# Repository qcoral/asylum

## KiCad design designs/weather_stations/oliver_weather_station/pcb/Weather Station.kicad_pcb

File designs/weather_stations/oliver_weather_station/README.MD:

# Oliver's Weather Station
A very basic prototype of a weather station using a Wemos C3 Mini and a 1.8" TFT display. 
Code will be heavily improved once I have access to the physical hardware to test!

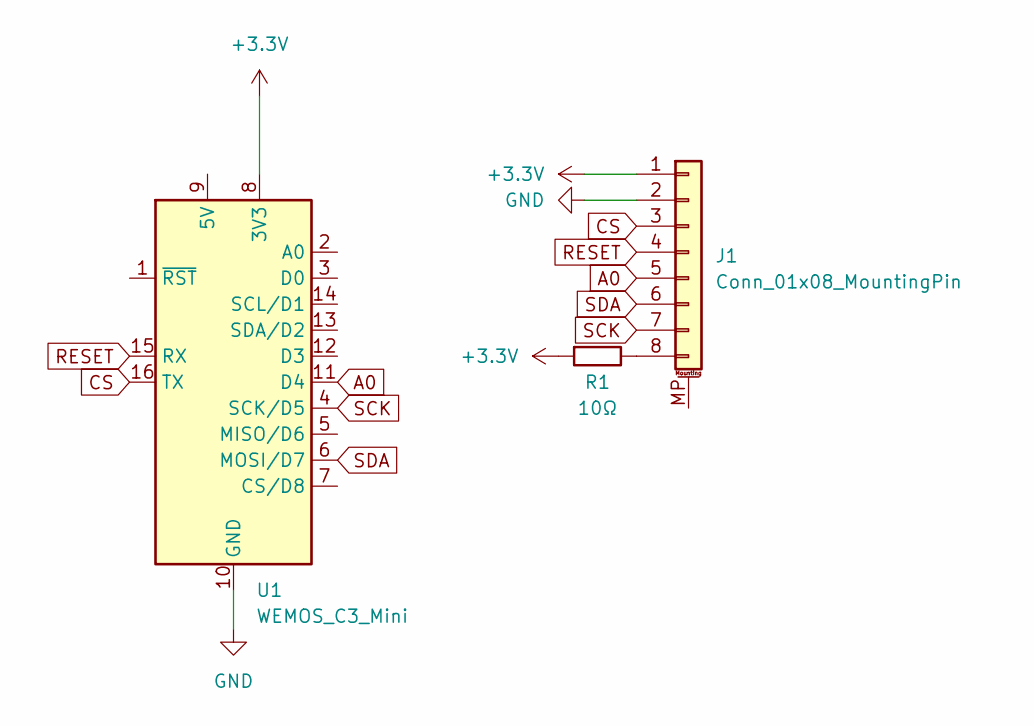
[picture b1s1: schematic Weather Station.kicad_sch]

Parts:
J1: Conn_01x08_MountingPin; PinHeader_1x08_P2.54mm_Vertical
R1: 10Ω; R_Axial_DIN0207_L6.3mm_D2.5mm_P10.16mm_Horizontal
U1: WEMOS_C3_Mini; WEMOS_D1_mini_light

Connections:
+3.3V: J1.1, R1.1, U1.8 (3V3)
A0: J1.5, U1.11 (D4)
CS: J1.3, U1.16 (TX)
GND: J1.2, U1.10 (GND)
unnamed: J1.8, R1.2
RESET: J1.4, U1.15 (RX)
SCK: J1.7, U1.4 (SCK/D5)
SDA: J1.6, U1.6 (MOSI/D7)

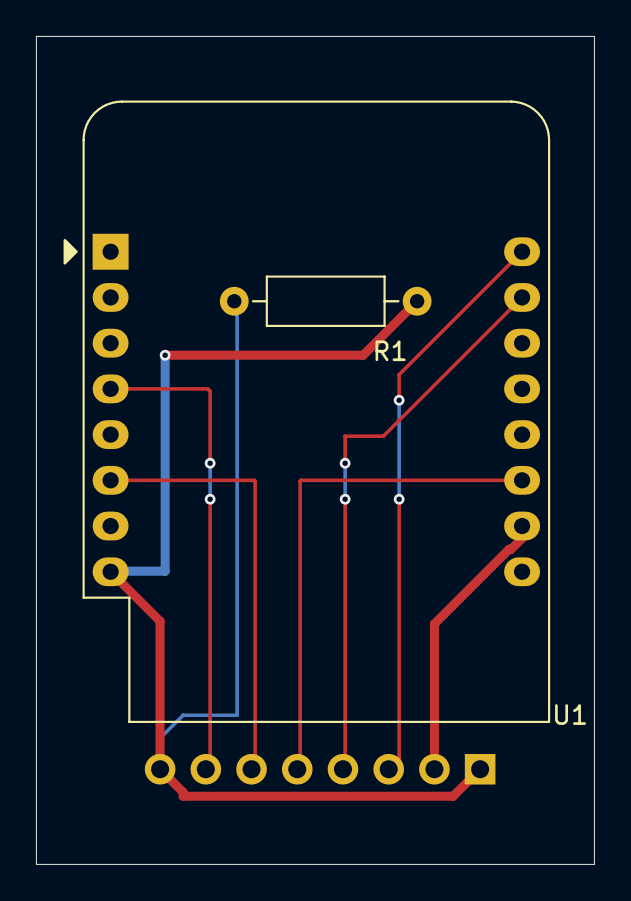
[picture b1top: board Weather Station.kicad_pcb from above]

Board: 2 copper layers, 31.0 x 46.0 mm, 3 parts (1 on the bottom side), 8 nets.

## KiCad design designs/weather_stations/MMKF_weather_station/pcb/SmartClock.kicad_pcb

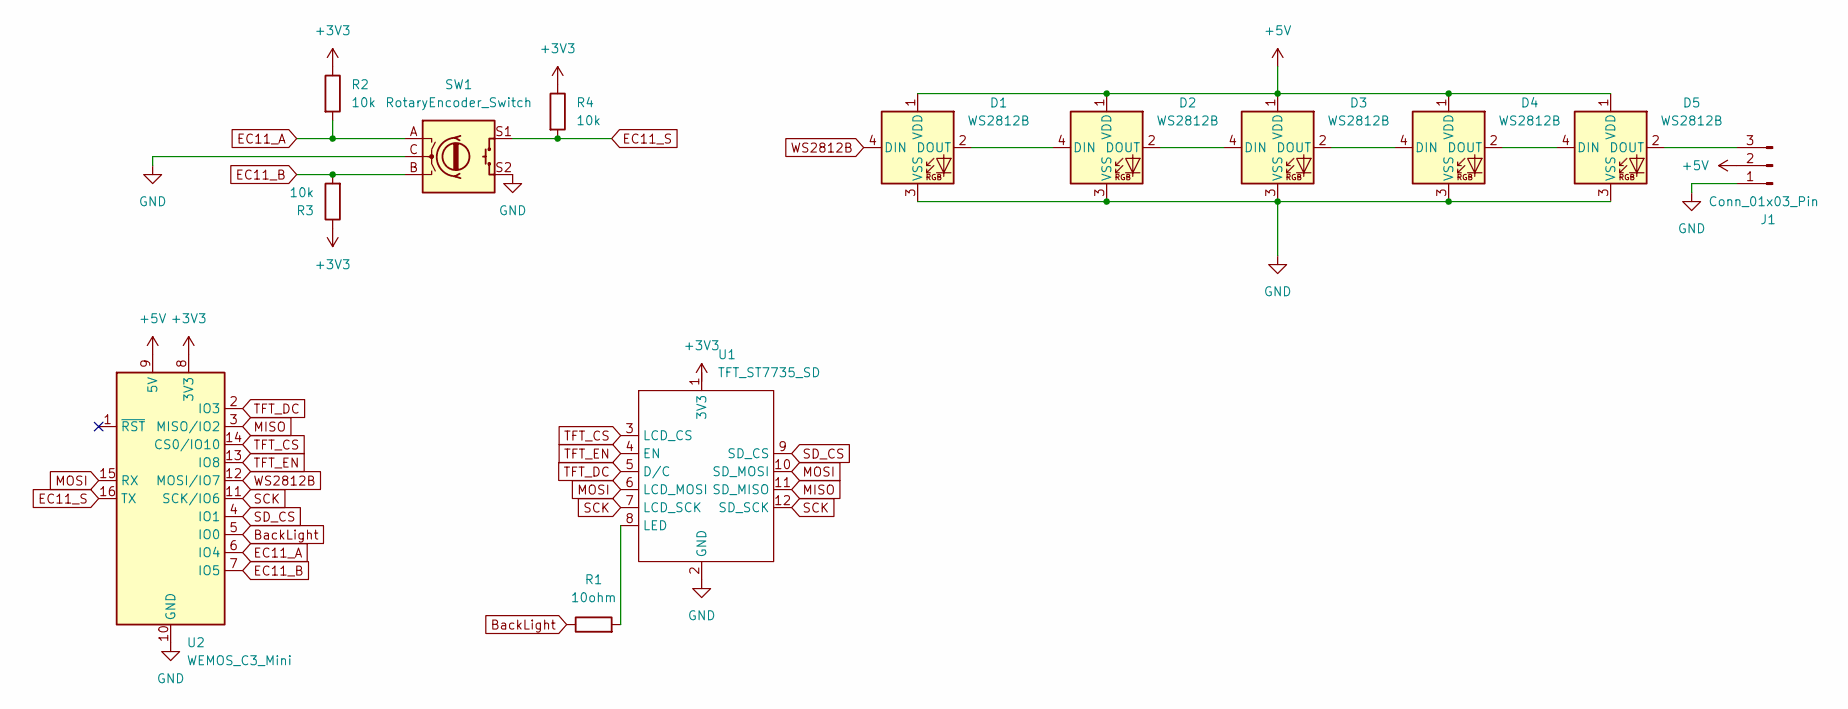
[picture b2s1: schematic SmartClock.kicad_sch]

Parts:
D1, D2, D3, D4, D5: WS2812B; LED_WS2812B_PLCC4_5.0x5.0mm_P3.2mm
J1: Conn_01x03_Pin; PinHeader_1x03_P2.54mm_Vertical
R1: 10ohm; Resistor_0402
R2, R3, R4: 10k; Resistor_0402
SW1: RotaryEncoder_Switch; RotaryEncoder_Alps_EC11E-Switch_Vertical_H20mm
U1: TFT_ST7735_SD
U2: WEMOS_C3_Mini; WEMOS_D1_mini_light

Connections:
+3V3: R2.1, R3.1, R4.1, U2.8 (3V3)
+5V: D1.1 (VDD), D2.1 (VDD), D3.1 (VDD), D4.1 (VDD), D5.1 (VDD), J1.2, U2.9 (5V)
BackLight: R1.1, U2.5 (IO0)
EC11_A: R2.2, SW1.A, U2.6 (IO4)
EC11_B: R3.2, SW1.B, U2.7 (IO5)
EC11_S: R4.2, SW1.S1, U2.16 (TX)
GND: D1.3 (VSS), D2.3 (VSS), D3.3 (VSS), D4.3 (VSS), D5.3 (VSS), J1.1, SW1.C, SW1.S2, U1.2 (GND), U2.10 (GND)
MISO: U1.11 (SD_MISO), U2.3 (MISO/IO2)
MOSI: U1.6 (LCD_MOSI), U1.10 (SD_MOSI), U2.15 (RX)
unnamed: D1.2 (DOUT), D2.4 (DIN)
unnamed: D2.2 (DOUT), D3.4 (DIN)
unnamed: D3.2 (DOUT), D4.4 (DIN)
unnamed: D4.2 (DOUT), D5.4 (DIN)
unnamed: D5.2 (DOUT), J1.3
unnamed: R1.2, U1.8 (LED)
SCK: U1.7 (LCD_SCK), U1.12 (SD_SCK), U2.11 (SCK/IO6)
SD_CS: U1.9 (SD_CS), U2.4 (IO1)
TFT_CS: U1.3 (LCD_CS), U2.14 (CS0/IO10)
TFT_DC: U1.5 (D/C), U2.2 (IO3)
TFT_EN: U1.4 (EN), U2.13 (IO8)
WS2812B: D1.4 (DIN), U2.12 (MOSI/IO7)

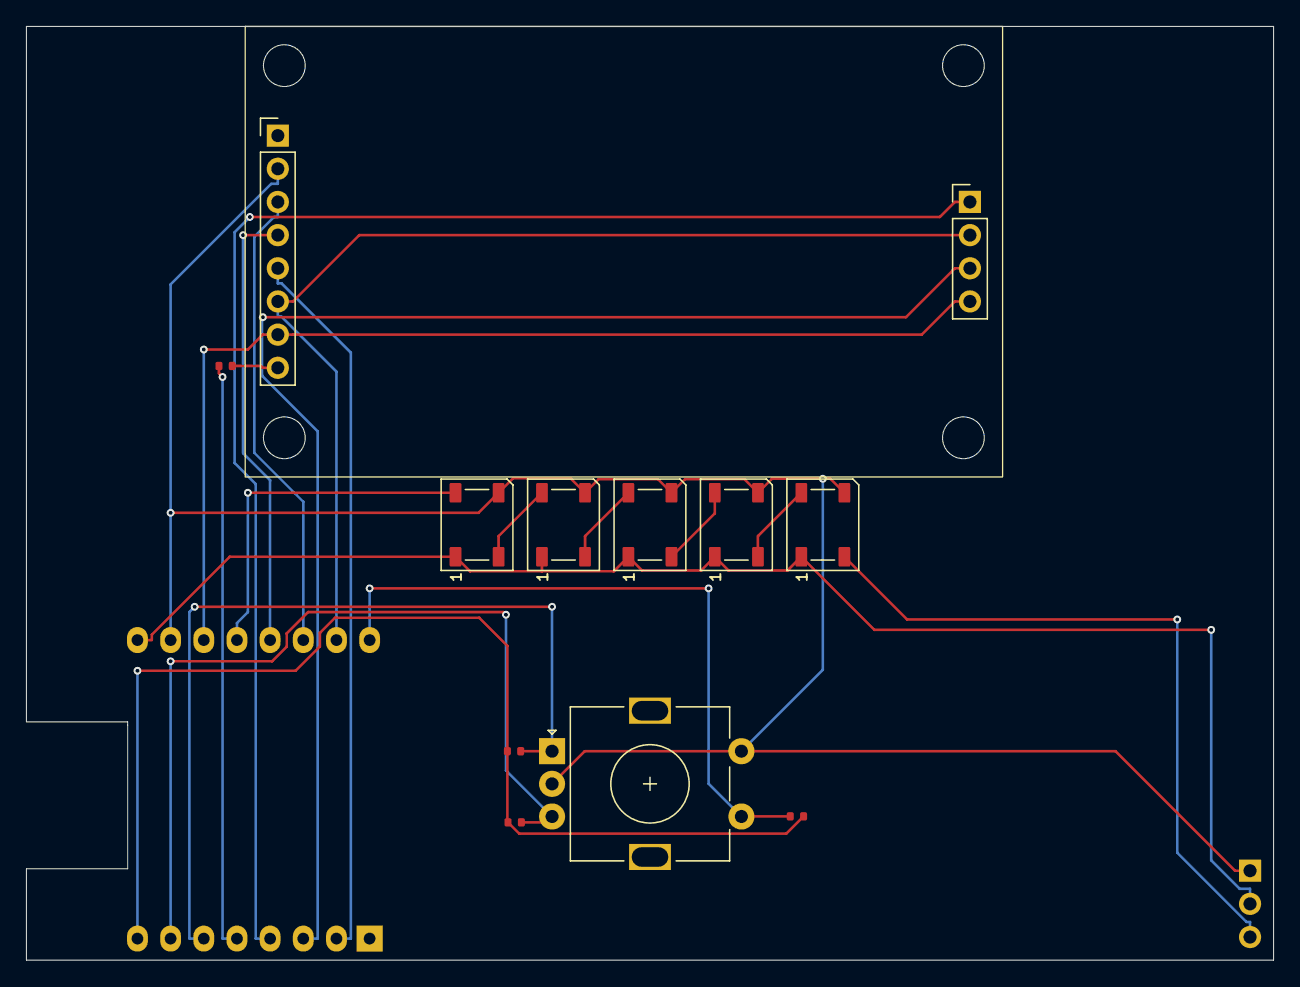
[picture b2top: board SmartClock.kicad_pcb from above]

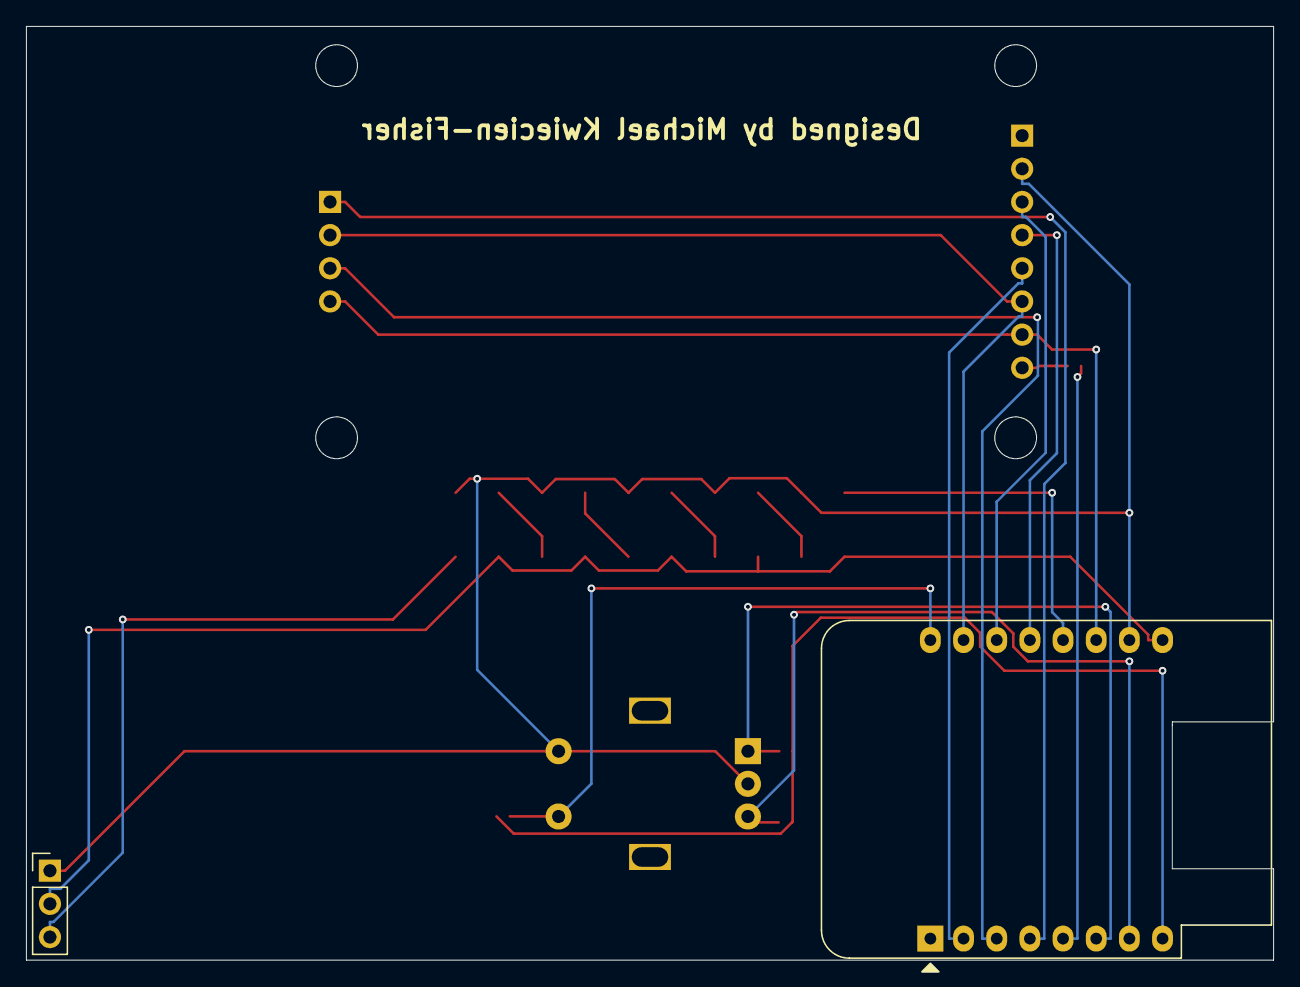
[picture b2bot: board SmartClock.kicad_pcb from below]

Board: 2 copper layers, 95.5 x 71.5 mm, 13 parts (2 on the bottom side), 21 nets.

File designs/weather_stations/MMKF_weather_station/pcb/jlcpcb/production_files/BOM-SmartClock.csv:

Comment,Designator,Footprint,LCSC,Quantity
WS2812B,D3,LED_WS2812B_PLCC4_5.0x5.0mm_P3.2mm,,1
WS2812B,D5,LED_WS2812B_PLCC4_5.0x5.0mm_P3.2mm,,1
WS2812B,D2,LED_WS2812B_PLCC4_5.0x5.0mm_P3.2mm,,1
10k,R4,Resistor_0402,,1
10k,R2,Resistor_0402,,1
WS2812B,D1,LED_WS2812B_PLCC4_5.0x5.0mm_P3.2mm,,1
10k,R3,Resistor_0402,,1
WS2812B,D4,LED_WS2812B_PLCC4_5.0x5.0mm_P3.2mm,,1
10ohm,R1,Resistor_0402,,1

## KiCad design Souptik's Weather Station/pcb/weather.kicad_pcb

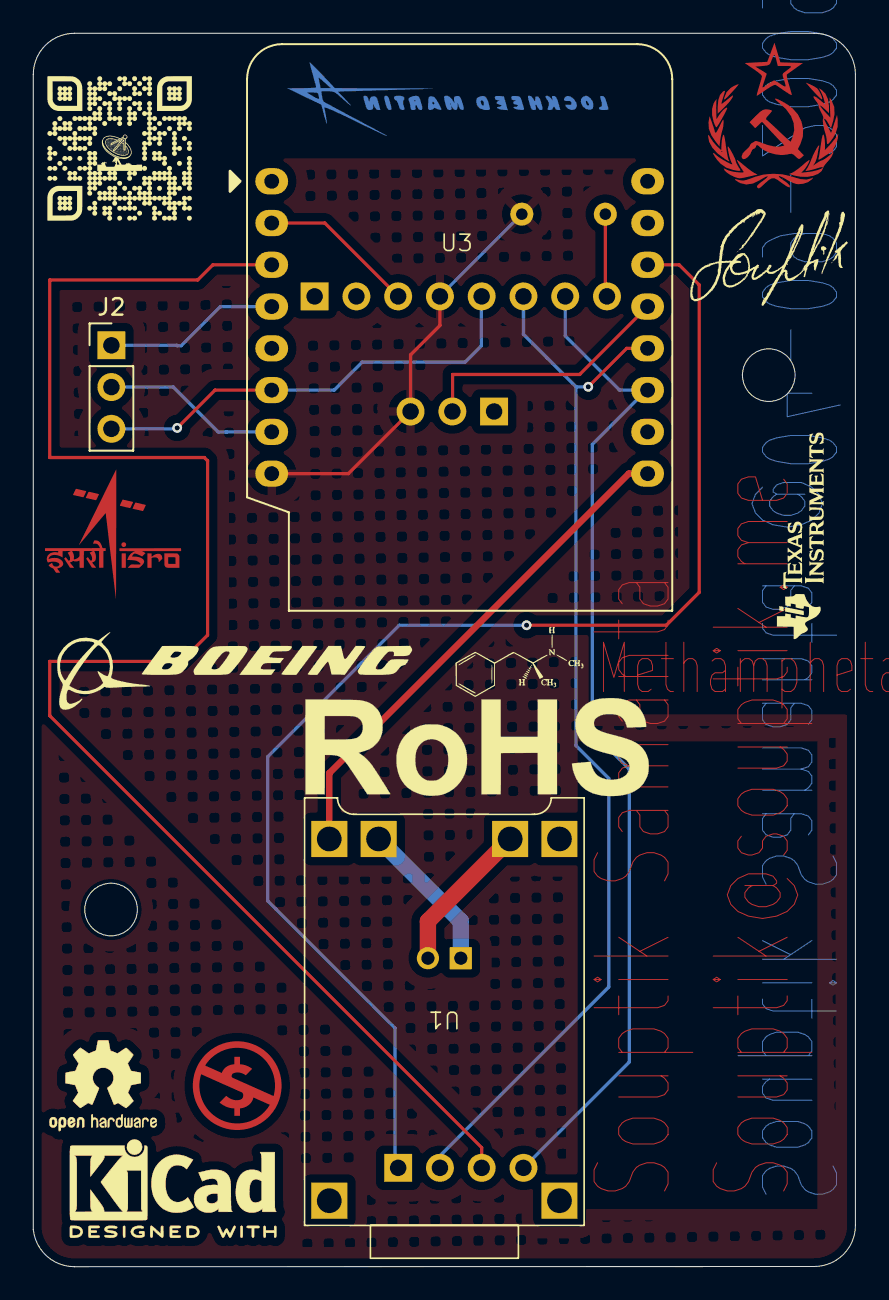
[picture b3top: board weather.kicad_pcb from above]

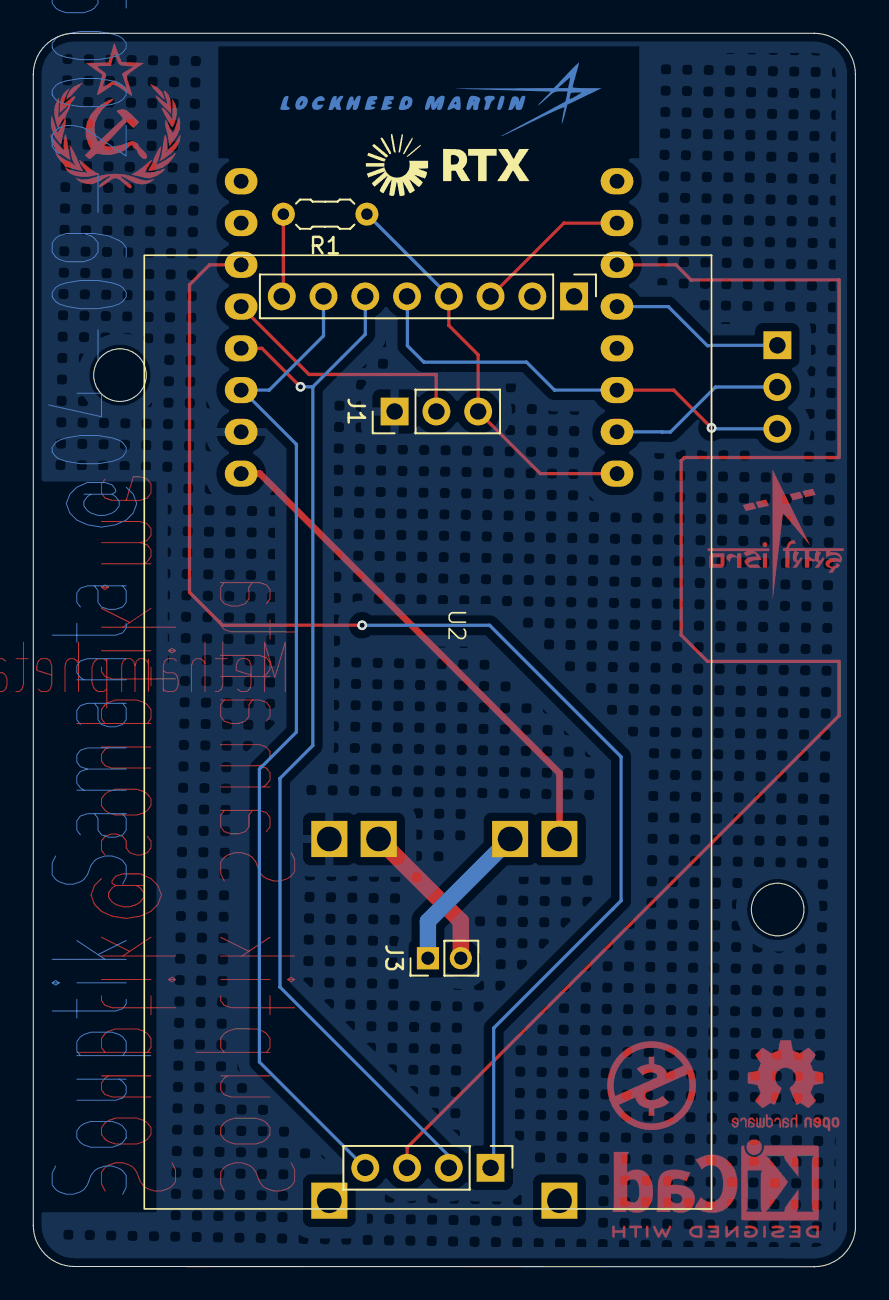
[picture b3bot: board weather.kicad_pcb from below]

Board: 2 copper layers, 50.0 x 75.0 mm, 7 parts (4 on the bottom side), 15 nets.

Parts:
J1: dht11; PinHeader_1x03_P2.54mm_Vertical
J2: EXTRA PINS; PinHeader_1x03_P2.54mm_Vertical
J3: Conn_01x02_Pin; PinHeader_1x02_P2.00mm_Vertical
R1: 10; R_Axial_DIN0204_L3.6mm_D1.6mm_P5.08mm_Horizontal
U1: TP4056
U2: TFT_ST7735_SD
U3: WEMOS_C3_Mini; WEMOS_C3_mini

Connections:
5V: U1.2 (OUT+), U3.9 (5V)
GND: J1.1, U1.3 (OUT-), U3.10 (GND)
IO1: J2.1, U3.4 (IO1)
IO3: U2.3 (LCD_CS), U3.2 (IO3)
IO4: J2.3, U2.5 (D/C), U3.6 (IO4)
IO5: J2.2, U3.7 (IO5)
IO10: U2.9 (SD_CS), U3.14 (CS0/IO10)
MISO: U2.11 (SD_MISO), U3.3 (MISO/IO2)
MOSI: U2.6 (LCD_MOSI), U2.10 (SD_MOSI), U3.12 (MOSI/IO7)
unnamed: J3.1, U1.0 (BAT+)
unnamed: J3.2, U1.1 (BAT-)
unnamed: R1.2, U2.8 (LED)
SCK: U2.7 (LCD_SCK), U2.12 (SD_SCK), U3.11 (SCK/IO6)
SIGD: J1.2, U3.13 (IO8)
VCC: J1.3, R1.1, U2.4 (EN), U3.8 (3V3)

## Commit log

2024-12-16 hehe
2024-12-18 Add cyaopad
2024-12-18 Update cyaopad to latest
2024-12-19 Aniweather: Add another diode to improve current capactiy
2024-12-20 Add MMKF weather station
2024-12-20 Rename 3DShell_PCB_PCB_Desky_2024-12-20.zip to 3DShell.zip
2024-12-20 Rename Gerber_Desky_PCB_Desky_2024-12-20.zip to Gerber.zip
2024-12-20 Rename Schematic_Desky_2024-12-20.pdf to Schematic.pdf
2024-12-20 Uploading all files
2024-12-20 Added PCB Files to PCB folder
2024-12-20 Create ignor
2024-12-20 Added Aeroportal
2024-12-20 Add submission files
    Add all files
2024-12-21 Create first
2024-12-21 upload files for oliver's weather station
